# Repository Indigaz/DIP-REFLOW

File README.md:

# DIP-REFLOW
An all through-hole, Arduino powered, reflow oven controller.

Have you ever wondered why most toaster oven reflow controllers require a shield on a development board,
or the controller has a number of surface mounted components on the PCB?  I did too and I didn't want to
sacrifice a development board, that I frequently use and tear apart, into a long-term installation such
as a reflow controller.

This reflow controller is based on RocketScream's Arduino shield based reflow controller, however, this is
a fully hand solderable, all through-hole implementaion.  It makes use of a MAX31855 breakout board
available from Adafruit (http://www.adafruit.com/product/269) to read the K-type thermocouple.

The Arduino code has been pieced together from several sources to add the features and to get the 
functionality that I was looking for. 

**I still need to finish up a Bill-of-Materials list and cleanup the code somewhat.  Boards will be available on
OSHPark for a quick purchase or you can send off the .BRD file to your fab shop of choice.  I'll also look
at rendering a quality PDF file for those that might want to try and hand craft the PCB at home.  Note, this is
a two sided board.**

I will have this project also tracked at http://hackaday.io for more information such as assembly photos.

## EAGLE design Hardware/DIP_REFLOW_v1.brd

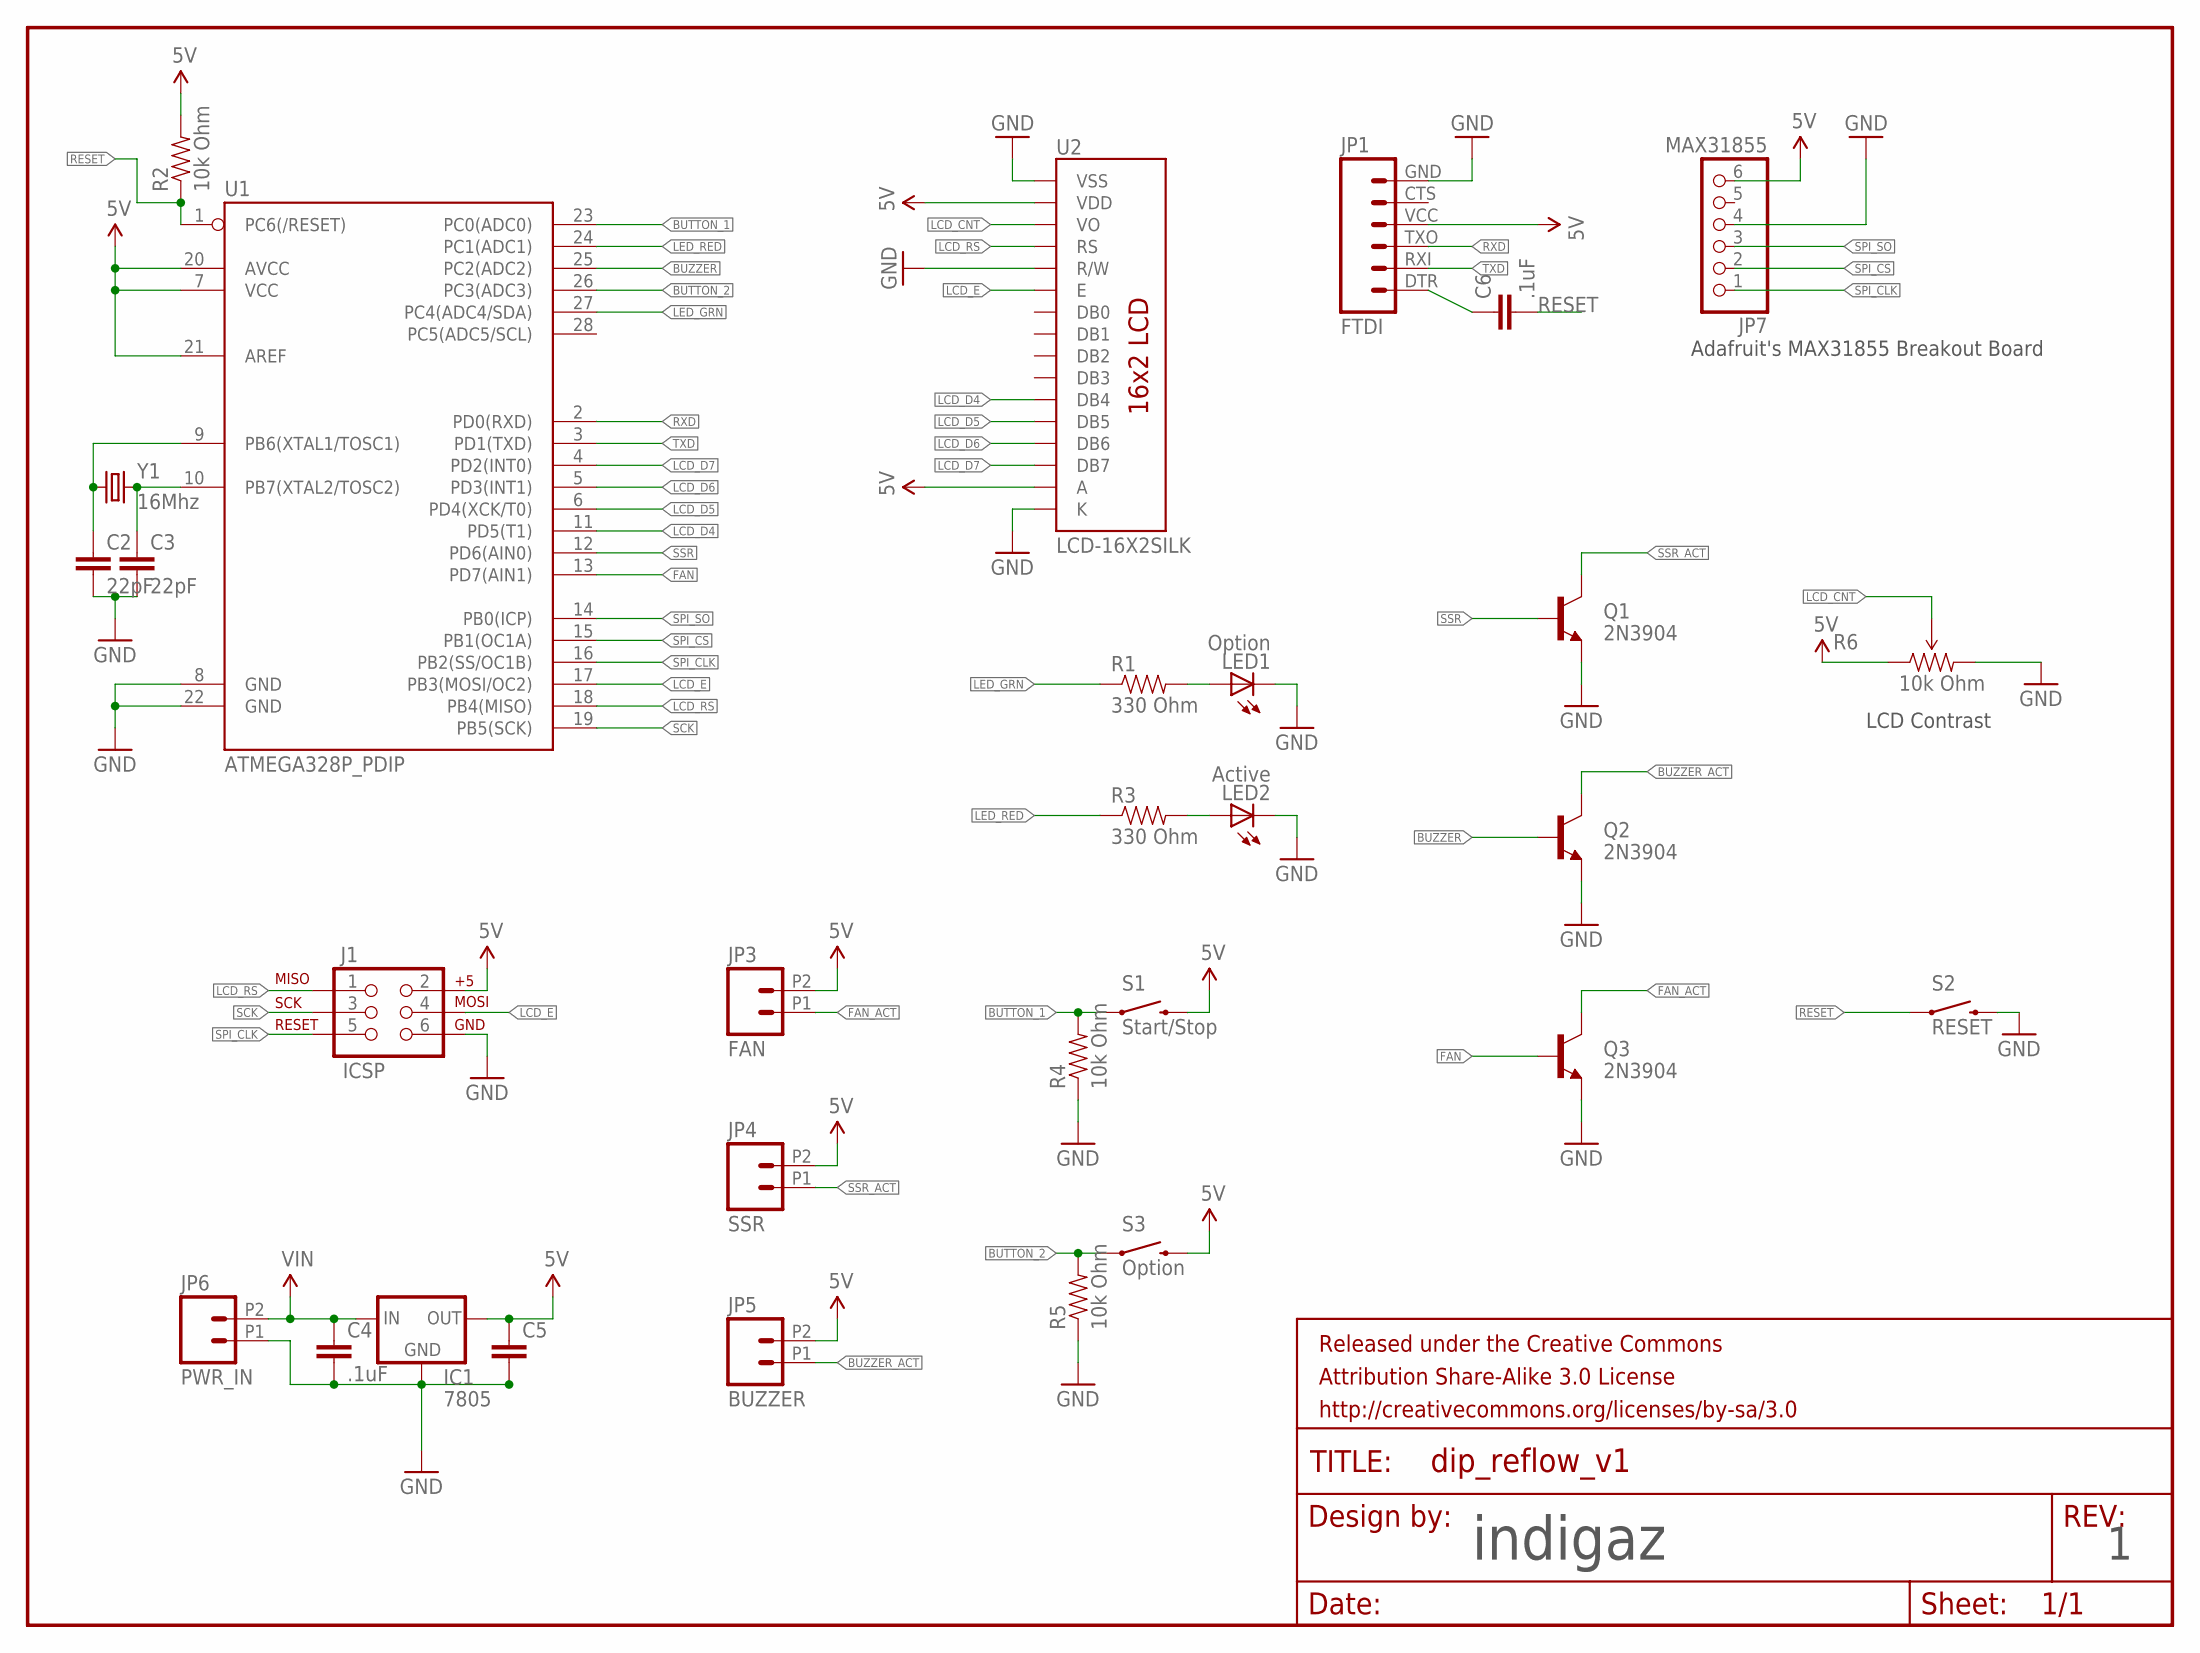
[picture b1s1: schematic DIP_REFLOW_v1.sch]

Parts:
C2, C3: 22pF; CAP-PTH-5MM
C4, C6: .1uF; CAP-PTH-5MM
C5: CAPPTH1; CAP-PTH-5MM
FRAME1: FRAME-LETTER; CREATIVE_COMMONS
IC1: 7805; TO-220-ALT
J1: ICSP; 2X3
JP1: FTDI; FTDI_BASIC
JP3: FAN; 1X02_2.54_SCREWTERM
JP4: SSR; 1X02_2.54_SCREWTERM
JP5: BUZZER; 1X02_2.54_SCREWTERM
JP6: PWR_IN; 1X02_2.54_SCREWTERM
JP7: MAX31855; 1X06
LED1: Option; LED5MM
LED2: Active; LED5MM
Q1, Q2, Q3: 2N3904; TO-92-AMMO
R1, R3: 330 Ohm; AXIAL-0.4
R2, R4, R5: 10k Ohm; AXIAL-0.4
R6: 10k Ohm; 3386U
S1: Start/Stop; TACTILE-PTH
S2: RESET; TACTILE-PTH
S3: Option; TACTILE-PTH
U1: ATMEGA328P_PDIP; DIL28-3
U2: LCD-16X2SILK; LCD-16X2
Y1: 16Mhz; HC49US

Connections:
5V: C5.1, IC1.OUT, J1.2, JP1.VCC (4), JP3.P2 (2), JP4.P2 (2), JP5.P2 (2), JP7.6, R2.P$2 (2), R6.1 (CCW), S1.3 (2), S3.3 (2), U1.7 (VCC), U1.20 (AVCC), U1.21 (AREF), U2.2 (VDD), U2.15 (A)
BUTTON_1: R4.P$2 (2), S1.1, U1.23 (PC0(ADC0))
BUTTON_2: R5.P$2 (2), S3.1, U1.26 (PC3(ADC3))
BUZZER: Q2.2 (B), U1.25 (PC2(ADC2))
BUZZER_ACT: JP5.P1 (1), Q2.3 (C)
FAN: Q3.2 (B), U1.13 (PD7(AIN1))
FAN_ACT: JP3.P1 (1), Q3.3 (C)
GND: C2.2, C3.2, C4.2, C5.2, IC1.GND, J1.6, JP1.GND (6), JP6.P1 (1), JP7.4, LED1.K (C), LED2.K (C), Q1.1 (E), Q2.1 (E), Q3.1 (E), R4.P$1 (1), R5.P$1 (1), R6.3 (CW), S2.3 (2), U1.8 (GND), U1.22 (GND), U2.1 (VSS), U2.5 (R/W), U2.16 (K)
LCD_CNT: R6.2 (WIPER), U2.3 (VO)
LCD_D4: U1.11 (PD5(T1)), U2.11 (DB4)
LCD_D5: U1.6 (PD4(XCK/T0)), U2.12 (DB5)
LCD_D6: U1.5 (PD3(INT1)), U2.13 (DB6)
LCD_D7: U1.4 (PD2(INT0)), U2.14 (DB7)
LCD_E: J1.4, U1.17 (PB3(MOSI/OC2)), U2.6 (E)
LCD_RS: J1.1, U1.18 (PB4(MISO)), U2.4 (RS)
LED_GRN: R1.P$1 (1), U1.27 (PC4(ADC4/SDA))
LED_RED: R3.P$1 (1), U1.24 (PC1(ADC1))
unnamed: C6.1, JP1.DTR (1)
unnamed: C2.1, U1.9 (PB6(XTAL1/TOSC1)), Y1.1
unnamed: LED1.A, R1.P$2 (2)
unnamed: C3.1, U1.10 (PB7(XTAL2/TOSC2)), Y1.2
unnamed: LED2.A, R3.P$2 (2)
RESET: C6.2, R2.P$1 (1), S2.1, U1.1 (PC6(/RESET))
RXD: JP1.TXO (3), U1.2 (PD0(RXD))
SCK: J1.3, U1.19 (PB5(SCK))
SPI_CLK: J1.5, JP7.1, U1.16 (PB2(SS/OC1B))
SPI_CS: JP7.2, U1.15 (PB1(OC1A))
SPI_SO: JP7.3, U1.14 (PB0(ICP))
SSR: Q1.2 (B), U1.12 (PD6(AIN0))
SSR_ACT: JP4.P1 (1), Q1.3 (C)
TXD: JP1.RXI (2), U1.3 (PD1(TXD))
VIN: C4.1, IC1.IN, JP6.P2 (2)

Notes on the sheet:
indigaz
Adafruit's MAX31855 Breakout Board
LCD Contrast

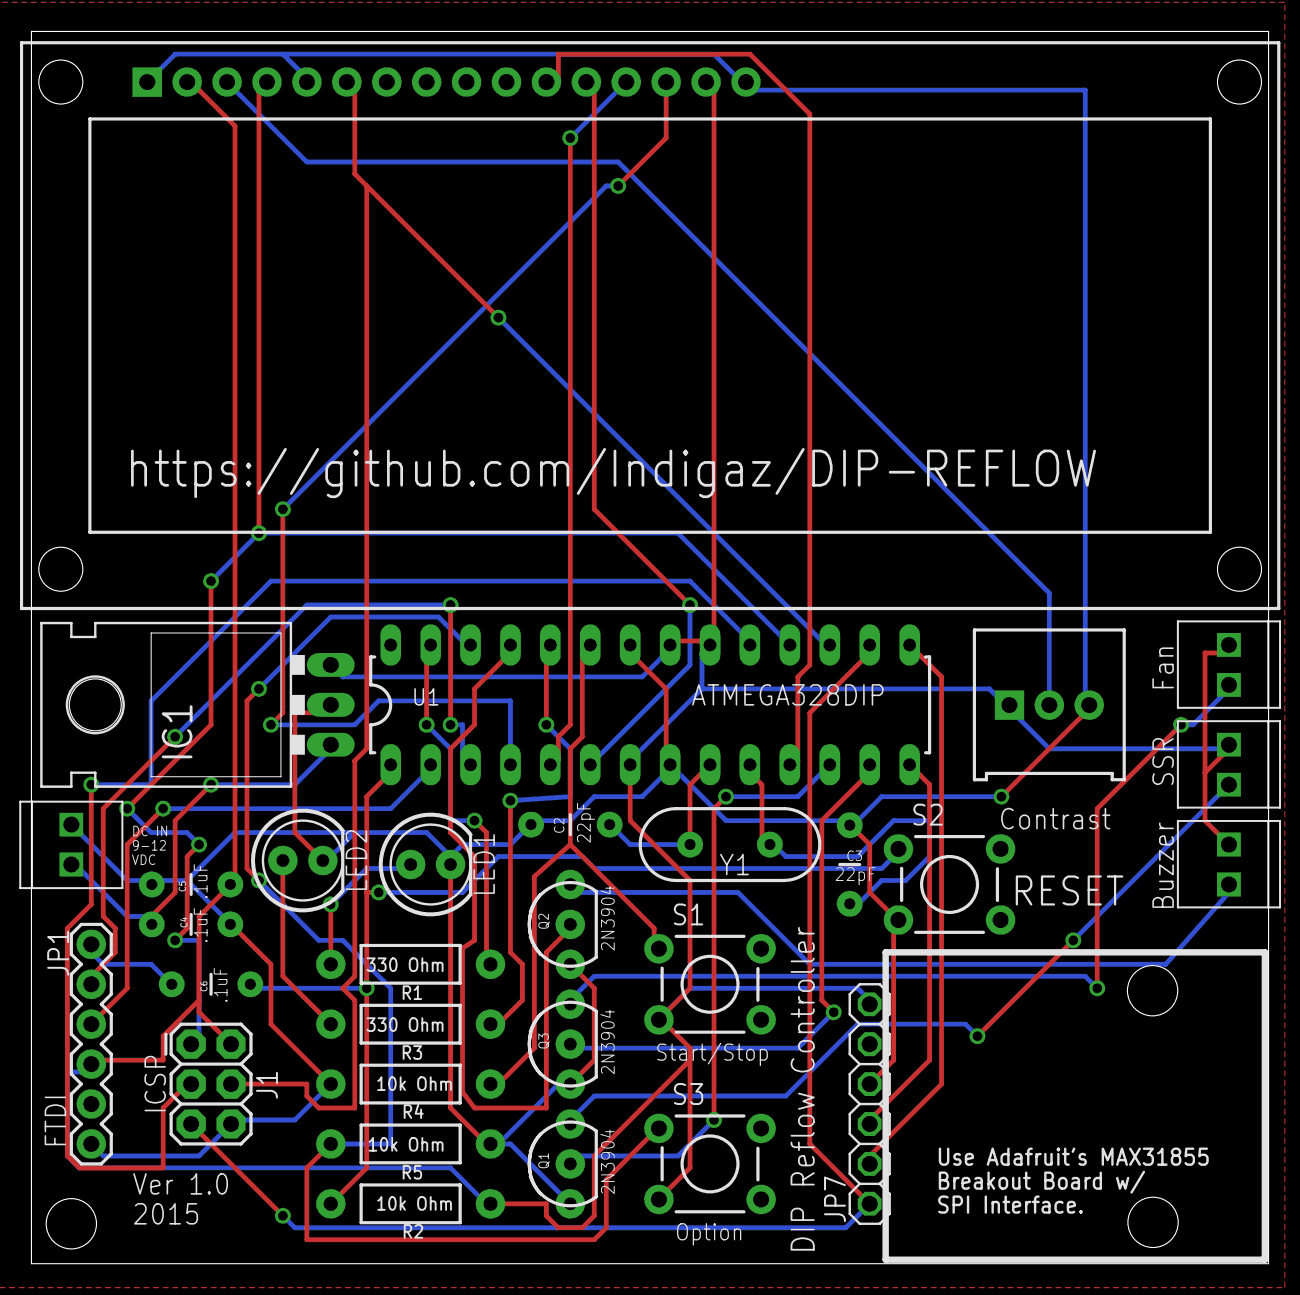
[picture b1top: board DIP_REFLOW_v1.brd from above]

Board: 2 copper layers, 78.7 x 78.4 mm, 31 parts (0 on the bottom side), 32 nets.

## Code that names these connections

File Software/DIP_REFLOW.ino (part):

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// ***** PIN ASSIGNMENT *****
const int button1 = A0;
const int button2 = A3; // Not used at the moment.
const int ssr = 6;
const int buzzer = A2;
const int lcdRs = 12;
const int lcdE = 11;
const int lcdD4 = 5;
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
void setup()
{
  // SSR pin initialization to ensure reflow oven is off
  digitalWrite(ssr, LOW);
  pinMode(ssr, OUTPUT);

  // Buzzer pin initialization to ensure annoying buzzer is off
  digitalWrite(buzzer, LOW);
  pinMode(buzzer, OUTPUT);

  // LED pins initialization and turn on upon start-up (active low)
  //  digitalWrite(ledRed, LOW);
  digitalWrite(ledRed, HIGH);
  digitalWrite(ledGreen, LOW);
  //pinMode(fan, OUTPUT);
  pinMode(ledRed, OUTPUT);
  pinMode(ledGreen, OUTPUT);
  // Push button pins initialization
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
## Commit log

2015-02-01 :boom::camel: Added .gitattributes & .gitignore files
2015-02-01 Hardware files
    Uploading of DIP-REFLOW hardware files created in Eagle 6.4.
2015-02-01 Software files
    The Arduino code to run the reflow controller.
2015-02-01 Update to .BRD file.
2015-02-03 Updates and Fixes
2015-02-03 :information_source: BOM added!
2015-02-03 :100: Cleanup
    Removing some old files!

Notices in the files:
Software/DIP_REFLOW.ino:
This reflow oven controller hardware and firmware are released under the
Creative Commons Share Alike v3.0 license
http://creativecommons.org/licenses/by-sa/3.0
parts and their libraries:
SparkFun-Aesthetics: Licensing: CC v3.0 Share-Alike You are welcome to use this library for commercial purposes.
SparkFun-Aesthetics: Released under the Creative Commons Attribution Share-Alike 3.0 License
SparkFun-Aesthetics: Released under the Creative Commons
